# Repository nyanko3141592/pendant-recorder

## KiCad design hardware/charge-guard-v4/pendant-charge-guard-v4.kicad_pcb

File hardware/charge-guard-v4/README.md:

# Charge guard v4 — engineering prototype, not for order

Existing v3 remains unchanged for the separate fit-check chat. This revision adds12parts (87total) within18×33×0.8mm/6layers; case integration is not established. Final KiCad ERC0/DRC0/unconnected0/schematic parity0. Review `order-status.json` and the final DRC/ ERC reports rather than assuming completion from a router log.

## Electrical change

J2 pack NTC now feeds an independent ratiometric window comparator U12 (TLV7032DDFR). R37 excites the NTC from VBUS; R38/R39 and R40/R41 define provisional cold/hot thresholds. USB absence removes excitation, so these dividers do not consume battery current in intended operation.

U12A is high when NTC voltage is below the cold reference; U12B is high when above the hot reference. NTC open gives cold-not-OK; short gives hot-not-OK. The push-pull TLV7032 has POR-low outputs; the open-drain TLV7042 has POR-high-impedance and must NOT be substituted. [TI SLVSE13J, sections4.2,5.9,6.4](https://www.ti.com/lit/ds/symlink/tlv7042.pdf).

Q2 clamps charger TS low by default through R12's VBUS pull-up. Q4/Q5/Q6 form a series permission path to release Q2 only when MCU CHG_ALLOW and both comparator outputs are high. R36 keeps CHG_ALLOW low at reset. MCU GPIO is no longer directly tied to the inhibit gate; no5V GPIO pull-up is introduced. Body diode orientation of each series NMOS opposes the downward current when off.

Charger TS uses R35=10k to GND when released. This prevents the intended circuit from leaving TS floating. The existing BQ25101 permits TTDM with a floating/high TS, which disables temperature monitoring/timer/termination: [TI SLUSBV8C pin table](https://www.ti.com/lit/ds/symlink/bq25101.pdf). The NTC is no longer placed directly on that pin. Charge voltage/current regulation remains BQ25101; external guard replaces its temperature decision.

## What the analysis does and does not establish

`check_guard.py` checks actual net assignments, all8Boolean permission combinations, open/short faults, and resistor/comparator-error DC corners. Hypothetical R25=9..11k and beta2000..5000K produce conditional cold trips10.05..24.34°C and hot trips25.52..41.21°C. These are sensitivity bounds, NOT the actual XE temperature limits or a supplier-qualified guarantee. The broad uncertainty can leave only a narrow usable range; do not publish this as the final user operating range.

The33mV total comparator error allowance is a design assumption. TI's dual electrical table covers1.8..5V, whereas the study includes5.25V USB; manufacturer confirmation/bench characterization is needed. Actual NTC beta/R-T tolerances, thermal lag/self-heating, MOS leakage, switching thresholds, power ramp timing, TS disable levels and brownouts still require qualification. Nominal5V divider consumption is about0.75mA from USB (including inhibit pull-up when released), and typical NTC dissipation near25°C is0.625mW; pack thermal effect is unknown.

No charging permission may be enabled in released firmware until the battery-specific guard configuration and charge voltage/termination conditions are approved. During boot/reset/suspend/error, CHG_ALLOW stays low. Normal USB insertion must preserve recording and must not request USB sync.

## Reproduction

1. `python3 hardware/tools/create_charge_guard_v4.py` creates schematic/BOM/connection table (overwrites those files).
2. KiCad Python `hardware/tools/prepare_charge_guard_board.py` makes a new unrouted seed from v3.
3. KiCad Python `hardware/tools/layout_charge_guard_v4.py --discard-routing` packs the87parts and exports route.dsn. This overwrites this revision's board.
4. Freerouting2.5.0: `-de route.dsn -do route.ses -mp25 --router.optimizer.enabled=false`.
5. Import with the dedicated tool, normalize minimum width0.10mm, apply `hardware/tools/finish_charge_guard_v4.py`, then run KiCad DRC with schematic parity and ERC. The repair moves shared endpoints/vias0.015..0.030mm, keeping0.10mm clearance.
6. `python3 hardware/charge-guard-v4/check_guard.py` regenerates the conditional DC analysis.

All additions require assembled-board sourcing/DFM. `sourcing-delta.json` lists catalog candidates, not reserved stock or an accepted order BOM. The earlier pending charge-voltage, termination, firmware, USB/SI and actual harness constraints remain.

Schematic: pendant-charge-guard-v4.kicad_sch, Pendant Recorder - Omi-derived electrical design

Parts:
C1, C2, C3, C6, C9, C22, C23, C24, C26: 100n; C_0402_1005Metric
C4: 10u; C_0603_1608Metric
C5, C15: 4.7u; C_0603_1608Metric
C7, C16, C18, C19, C25: 1u; C_0402_1005Metric
C11, C12: 10p tentative; C_0402_1005Metric
C13: 2.2u 10V; C_0402_1005Metric
C14: 2.2u; C_0402_1005Metric
C27: 22u effective TBD; C_0603_1608Metric
C28: 10n; C_0402_1005Metric
C29: 100n 10V; C_0402_1005Metric
D1: red LED; LED_0402_1005Metric
D2: BAT54WS (candidate; leakage/forward drop review p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; D_SOD-323
D6: amber LED 0402 TBD; LED_0402_1005Metric
J1: USB4105-GF-A (candidate); USB_C_GCT_USB4105_GroundLand112
J2: 0781710003 / DTP401525-XE; Molex_Pico-EZmate_78171-0003_1x03-1MP_P1.20mm_Vertical
J3: TC2030 SWD target pads; Tag-Connect_TC2030-IDC-NL_2x03_P1.27mm_Vertical
Q1: DMP2035U (candidate; power path review pending); SOT-23
Q2: 2N7002 (charge inhibit); SOT-23
Q3: 2N7002 (VBUS detect); SOT-23
Q4, Q5, Q6: 2N7002; SOT-23
R1: 0R; R_0402_1005Metric
R2: 10k; R_0402_1005Metric
R3, R4, R11, R12, R13, R15, R16, R17, R22, R36: 100k; R_0402_1005Metric
R5: 3.3k; R_0402_1005Metric
R6, R7: 5.1k 1%; R_0402_1005Metric
R8, R9: 0R tuning; R_0402_1005Metric
R10: 6.19k 1%; R_0402_1005Metric
R14: 1M; R_0402_1005Metric
R21, R23: 22R tentative; R_0402_1005Metric
R24, R25, R28: 47k; R_0402_1005Metric
R32: 6.8k tentative; R_0402_1005Metric
R33, R34: 1M 1%; R_0402_1005Metric
R35, R37, R38, R40: 10k 1%; R_0402_1005Metric
R39: 12.1k 1%; R_0402_1005Metric
R41: 8.25k 1%; R_0402_1005Metric
SW1: B3U-1000P (candidate); SW_SPST_B3U-1000P
TP1, TP2, TP3, TP4, TP5, TP6: TestPoint; TestPoint_Pad_D1.0mm
U1: STM32U535CEU6; QFN-48-1EP_7x7mm_P0.5mm_EP5.6x5.6mm
U2: USBLC6-2P6; SOT-666
U3: BQ25101YFPR; BQ25101_YFP6
U4: TPS7A0233PDBVR; SOT-23-5
U6: TPS7A0218PDBVR; SOT-23-5
U8: T5838; T5838_LGA7_BottomPort
U9: TXS0104ERUTR; Texas_R-PUQFN-N12
U10: TPS22916CYFPR; TPS22916_YFP4
U11: CSNP32GCR01-BOW; CSNP32GCR01_LGA8
U12: TLV7032DDFR; SOT-23-8
Y1: 32.768kHz CL=7pF TBD; Crystal_SMD_2012-2Pin_2.0x1.2mm

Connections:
/ALLOW_CHAIN_1: Q4.3 (D), Q5.2 (S)
/ALLOW_CHAIN_2: Q5.3 (D), Q6.2 (S)
/BAT: C14.1, J2.1 (PACK+), Q1.3 (D), R33.1, TP1.1, U3.A1 (OUT)
/BAT_ADC: C28.1, R33.2, R34.1, U1.11 (PA1)
/BAT_TS: J2.2 (PACK_NTC), R37.2, U12.2 (INA-), U12.5 (INB+)
/BOOT0: R3.1, U1.44 (PH3)
/BUTTON_N: R4.2, SW1.1, U1.26 (PB13)
/CC1: J1.A5 (CC1), R6.1
/CC2: J1.B5 (CC2), R7.1
/CHARGER_TS: Q2.3 (D), R35.1, U3.B1 (TS)
/CHG_ALLOW: Q4.1 (G), R36.1, U1.20 (PB2)
/CHG_INHIBIT_GATE: Q2.1 (G), Q6.3 (D), R12.2
/CHG_N: R11.2, U1.27 (PB14), U3.C1 (CHG)
/GND: C1.2, C2.2, C3.2, C4.2, C5.2, C6.2, C7.2, C9.2, C11.2, C12.2, C13.2, C14.2, C15.2, C16.2, C18.2, C19.2, C22.2, C23.2, C24.2, C25.2, C26.2, C27.2, C28.2, C29.2, D1.1 (K), D6.1 (K), J1.A1 (GND), J1.A12 (GND), J1.B1 (GND), J1.B12 (GND), J1.SH (SHIELD), J2.3 (PACK-), J3.5 (GND), Q2.2 (S), Q3.2 (S), Q4.2 (S), R3.2, R6.2, R7.2, R10.2, R14.2, R16.2, R17.2, R22.2, R34.2, R35.2, R36.2, R39.2, R41.2, SW1.2, TP6.1, U1.8 (VSSA), U1.23 (VSS), U1.35 (VSS), U1.47 (VSS), U1.49 (VSS), U2.2 (GND), U3.C2 (VSS), U4.2 (GND), U6.2 (GND), U8.2 (SELECT), U8.3 (GND), U9.6 (GND), U10.B1 (GND), U11.4 (VSS), U12.4 (VEE)
/ISET: R10.1, U3.B2 (ISET)
/LED_A: D1.2 (A), R5.2
/LSE_IN: C11.1, U1.3 (PC14), Y1.1
/LSE_OUT: C12.1, U1.4 (PC15), Y1.2
/MIC_CLK_1V8: U8.6 (CLK), U9.5 (A4)
/MIC_DATA_1V8: U8.1 (DATA), U9.4 (A3)
/MIC_EN: R17.1, U1.41 (PB5), U6.3 (EN)
/MIC_THSEL: U1.13 (PA3), U9.9 (B2)
/MIC_THSEL_1V8: U8.5 (THSEL), U9.3 (A2)
/MIC_WAKE: U1.12 (PA2), U9.10 (B1)
/MIC_WAKE_1V8: U8.4 (WAKE), U9.2 (A1)
/NRST: C9.1, J3.3 (nRESET), R2.2, U1.7 (NRST)
/PDM_CLK: R21.2, U9.7 (B4)
/PDM_CLK_MCU: R21.1, U1.39 (PB3)
/PDM_DATA: U1.40 (PB4), U9.8 (B3)
/REC_LED: R5.1, U1.25 (PB12)
/SD_CLK: R23.2, U11.3 (CLK)
/SD_CLK_MCU: R23.1, U1.15 (PA5)
/SD_CS_N: R28.2, U1.14 (PA4), U11.2 (CS_N)
/SD_EN: R22.1, U1.18 (PB0), U10.B2 (ON)
/SD_MISO: R25.2, U1.16 (PA6), U11.6 (DO)
/SD_MOSI: R24.2, U1.17 (PA7), U11.5 (DI)
/SD_V3: C26.1, C27.1, R24.1, R25.1, R28.1, TP5.1, U10.A1 (VOUT), U11.8 (VCC)
/STATUS_LED: R32.1, U1.29 (PA8)
/STATUS_LED_A: D6.2 (A), R32.2
/SWCLK: J3.4 (SWCLK), U1.37 (PA14)
/SWDIO: J3.2 (SWDIO), U1.34 (PA13)
/SYS: C15.1, D2.1 (K), Q1.2 (S), TP2.1, U4.1 (IN), U4.3 (EN)
/TEMP_COLD_OK: Q5.1 (G), U12.1 (OUTA)
/TEMP_HOT_OK: Q6.1 (G), U12.7 (OUTB)
/TS_COLD_REF: R38.2, R39.1, U12.3 (INA+)
/TS_HOT_REF: R40.2, R41.1, U12.6 (INB-)
/USB_DM: J1.A7 (D-), J1.B7 (D-), R9.1, U2.3 (IO2), U2.4 (IO2)
/USB_DM_MCU: R9.2, U1.32 (PA11)
/USB_DP: J1.A6 (D+), J1.B6 (D+), R8.1, U2.1 (IO1), U2.6 (IO1)
/USB_DP_MCU: R8.2, U1.33 (PA12)
/V1V8: C18.1, C22.1, C23.1, TP4.1, U6.5 (OUT), U8.7 (VDD), U9.1 (VCCA), U9.12 (OE)
/V3V3: C1.1, C2.1, C3.1, C4.1, C16.1, C19.1, C24.1, C25.1, J3.1 (VTref), R1.1, R2.1, R4.1, R11.1, R15.1, TP3.1, U1.1 (VBAT), U1.24 (VDD), U1.36 (VDD), U1.48 (VDD), U4.5 (OUT), U6.1 (IN), U9.11 (VCCB), U10.A2 (VIN)
/VBUS: C13.1, C29.1, D2.2 (A), J1.A4 (VBUS), J1.A9 (VBUS), J1.B4 (VBUS), J1.B9 (VBUS), Q1.1 (G), R12.1, R13.1, R16.1, R37.1, R38.1, R40.1, U2.5 (VBUS), U3.A2 (IN), U12.8 (VCC)
/VBUS_GATE: Q3.1 (G), R13.2, R14.1
/VBUS_N: Q3.3 (D), R15.2, U1.10 (PA0)
/VCAP: C5.1, U1.22 (VCAP)
/VDDA: C6.1, C7.1, R1.2, U1.9 (VDDA)

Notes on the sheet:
01 MCU / RTC / UI
02 USB-C / CHARGER
03 POWER / FUEL GAUGE
04 AUDIO / SD / INDICATORS
ENGINEERING DRAFT - NOT FOR FABRICATION - See hardware/charge-guard-v4/README.md

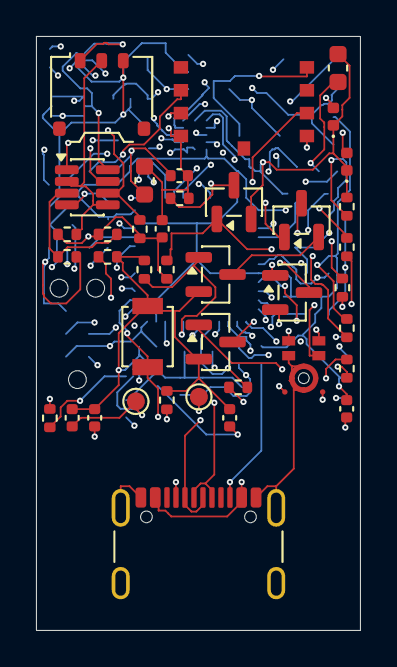
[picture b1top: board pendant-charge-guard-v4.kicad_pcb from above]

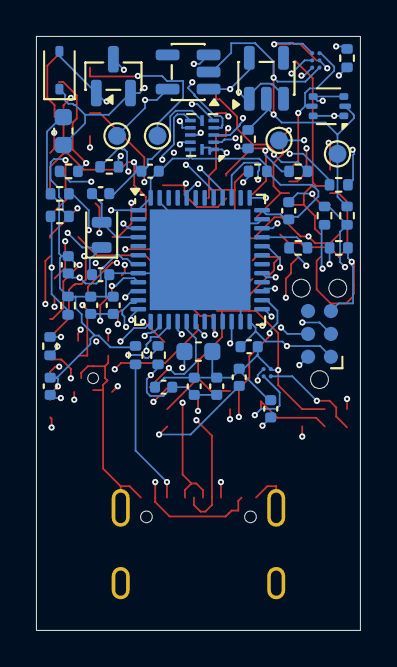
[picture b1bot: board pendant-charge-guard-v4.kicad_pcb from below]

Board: 6 copper layers, 18.0 x 33.0 mm, 87 parts (48 on the bottom side), 57 nets.

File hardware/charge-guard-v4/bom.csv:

Reference,Part/value,Footprint,Design note
U1,STM32U535CEU6,Package_DFN_QFN:QFN-48-1EP_7x7mm_P0.5mm_EP5.6x5.6mm,512KB Flash/274KB RAM; non-SMPS UFQFPN48. PB3/PB4 ADF AF3; PA5/6/7 SPI1 AF5. VDD USB shared 3.3V. JLC acceptance and pin review pending.
C1,100n,Capacitor_SMD:C_0402_1005Metric,
C4,10u,Capacitor_SMD:C_0603_1608Metric,Main bulk capacitor; check startup and effective capacitance.
C9,100n,Capacitor_SMD:C_0402_1005Metric,
R2,10k,Resistor_SMD:R_0402_1005Metric,
Y1,32.768kHz CL=7pF TBD,Crystal:Crystal_SMD_2012-2Pin_2.0x1.2mm,
C11,10p tentative,Capacitor_SMD:C_0402_1005Metric,
C12,10p tentative,Capacitor_SMD:C_0402_1005Metric,
J3,TC2030 SWD target pads,Connector:Tag-Connect_TC2030-IDC-NL_2x03_P1.27mm_Vertical,TC2030-NL/CTX standard; completed STM32-compatible probe/cable; access with battery disconnected.
SW1,B3U-1000P (candidate),Button_Switch_SMD:SW_SPST_B3U-1000P,
R4,100k,Resistor_SMD:R_0402_1005Metric,
R5,3.3k,Resistor_SMD:R_0402_1005Metric,
D1,red LED,LED_SMD:LED_0402_1005Metric,
J1,USB4105-GF-A (candidate),PendantD1:USB_C_GCT_USB4105_GroundLand112,Exact footprint and shield pad numbering pending connector selection
R6,5.1k 1%,Resistor_SMD:R_0402_1005Metric,
R7,5.1k 1%,Resistor_SMD:R_0402_1005Metric,
R8,0R tuning,Resistor_SMD:R_0402_1005Metric,STM32 integrated USB termination; external series value validate against ST USB layout guidance.
R9,0R tuning,Resistor_SMD:R_0402_1005Metric,STM32 integrated USB termination; external series value validate against ST USB layout guidance.
U2,USBLC6-2P6,Package_TO_SOT_SMD:SOT-666,"ST DS4260 same 6-pin function diagram; smaller package, LCSC C15999 catalog; orientation/land pattern final audit pending."
C13,2.2u 10V,Capacitor_SMD:C_0402_1005Metric,
U3,BQ25101YFPR,Pendant:BQ25101_YFP6,BQ25101 charge regulation retained; TS driven by independent hardware window guard and fixed10k. Not directly connected to pack NTC.
R10,6.19k 1%,Resistor_SMD:R_0402_1005Metric,"Nominal21.81mA, upper estimate23.66mA. XE charge current/termination/voltage acceptance not finalized."
R11,100k,Resistor_SMD:R_0402_1005Metric,
C14,2.2u,Capacitor_SMD:C_0402_1005Metric,
J2,0781710003 / DTP401525-XE,Connector_Molex:Molex_Pico-EZmate_78171-0003_1x03-1MP_P1.20mm_Vertical,"Pack NTC goes to separate window comparator, not charger TS. Beta/tolerances need supplier confirmation."
Q2,2N7002 (charge inhibit),Package_TO_SOT_SMD:SOT-23,Default-on TS clamp. Only MCU permission AND both hardware temperature permissions release it. Validate start-up transients.
R12,100k,Resistor_SMD:R_0402_1005Metric,100k VBUS pull-up defaults Q2 to charge inhibited; no MCU GPIO connection to5V.
D2,BAT54WS (candidate; leakage/forward drop review pending),Diode_SMD:D_SOD-323,USB path; characterize leakage and input inrush
Q1,DMP2035U (candidate; power path review pending),Package_TO_SOT_SMD:SOT-23,"S=SYS, D=BAT intentionally; body diode BAT -> SYS; exact MPN/pinout pending"
R16,100k,Resistor_SMD:R_0402_1005Metric,
C15,4.7u,Capacitor_SMD:C_0603_1608Metric,
U4,TPS7A0233PDBVR,Package_TO_SOT_SMD:SOT-23-5,3.3V main rail: 48-pin MCU has no separate USB supply; dropout/capacity measurement required.
U6,TPS7A0218PDBVR,Package_TO_SOT_SMD:SOT-23-5,DBV / SOT23-5 prototype; miniaturization later
C16,1u,Capacitor_SMD:C_0402_1005Metric,
C18,1u,Capacitor_SMD:C_0402_1005Metric,
C19,1u,Capacitor_SMD:C_0402_1005Metric,
R17,100k,Resistor_SMD:R_0402_1005Metric,
U8,T5838,Pendant:T5838_LGA7_BottomPort,BOTTOM port; 1.62..1.98V only; SELECT low = right channel
U9,TXS0104ERUTR,Package_DFN_QFN:Texas_R-PUQFN-N12,TI SCES651K Table 5-4 RUT pinout. UQFN procurement and PCBA acceptance pending.
R21,22R tentative,Resistor_SMD:R_0402_1005Metric,
C22,100n,Capacitor_SMD:C_0402_1005Metric,
C23,100n,Capacitor_SMD:C_0402_1005Metric,
C24,100n,Capacitor_SMD:C_0402_1005Metric,
U10,TPS22916CYFPR,Pendant:TPS22916_YFP4,Omi SD switch; power-off sequence must tristate ALL SD signals
R22,100k,Resistor_SMD:R_0402_1005Metric,
C25,1u,Capacitor_SMD:C_0402_1005Metric,
U11,CSNP32GCR01-BOW,Pendant:CSNP32GCR01_LGA8,SPI mode per manufacturer p2; unused DAT1/DAT2 reserved; verify power-up and interrupted-write behavior.
R23,22R tentative,Resistor_SMD:R_0402_1005Metric,
R24,47k,Resistor_SMD:R_0402_1005Metric,
R25,47k,Resistor_SMD:R_0402_1005Metric,
R28,47k,Resistor_SMD:R_0402_1005Metric,
C26,100n,Capacitor_SMD:C_0402_1005Metric,
C27,22u effective TBD,Capacitor_SMD:C_0603_1608Metric,
TP1,TestPoint,TestPoint:TestPoint_Pad_D1.0mm,
TP2,TestPoint,TestPoint:TestPoint_Pad_D1.0mm,
TP3,TestPoint,TestPoint:TestPoint_Pad_D1.0mm,
TP4,TestPoint,TestPoint:TestPoint_Pad_D1.0mm,
TP5,TestPoint,TestPoint:TestPoint_Pad_D1.0mm,
TP6,TestPoint,TestPoint:TestPoint_Pad_D1.0mm,
R32,6.8k tentative,Resistor_SMD:R_0402_1005Metric,"LED current target 0.1-0.2mA; verify LED Vf, daylight readability and GPIO limits"
D6,amber LED 0402 TBD,LED_SMD:LED_0402_1005Metric,Battery level by blink count; shared charging/error indication; exact LED MPN pending.
C2,100n,Capacitor_SMD:C_0402_1005Metric,
C3,100n,Capacitor_SMD:C_0402_1005Metric,
C5,4.7u,Capacitor_SMD:C_0603_1608Metric,
C6,100n,Capacitor_SMD:C_0402_1005Metric,
C7,1u,Capacitor_SMD:C_0402_1005Metric,
R1,0R,Resistor_SMD:R_0402_1005Metric,
R3,100k,Resistor_SMD:R_0402_1005Metric,
Q3,2N7002 (VBUS detect),Package_TO_SOT_SMD:SOT-23,
R13,100k,Resistor_SMD:R_0402_1005Metric,
R14,1M,Resistor_SMD:R_0402_1005Metric,
R15,100k,Resistor_SMD:R_0402_1005Metric,
R33,1M 1%,Resistor_SMD:R_0402_1005Metric,"Battery divider 1:2; sample after settling, calibrate with VREFINT; not coulomb counting."
R34,1M 1%,Resistor_SMD:R_0402_1005Metric,"Battery divider 1:2; sample after settling, calibrate with VREFINT; not coulomb counting."
C28,10n,Capacitor_SMD:C_0402_1005Metric,"Battery divider 1:2; sample after settling, calibrate with VREFINT; not coulomb counting."
R35,10k 1%,Resistor_SMD:R_0402_1005Metric,Holds normal TS level when released; no floating TS/TTDM in intended circuit.
R36,100k,Resistor_SMD:R_0402_1005Metric,MCU reset/high-Z defaults to no charging permission.
R37,10k 1%,Resistor_SMD:R_0402_1005Metric,Ratiometric NTC excitation only while USB present; self-heating must be verified.
R38,10k 1%,Resistor_SMD:R_0402_1005Metric,
R39,12.1k 1%,Resistor_SMD:R_0402_1005Metric,Provisional narrow window. Final values require actual pack R-T curve.
R40,10k 1%,Resistor_SMD:R_0402_1005Metric,
R41,8.25k 1%,Resistor_SMD:R_0402_1005Metric,Provisional narrow window. Final values require actual pack R-T curve.
U12,TLV7032DDFR,Package_TO_SOT_SMD:SOT-23-8,Push-pull variant intentionally selected: POR outputs low. Do not substitute TLV7042 open-drain (POR high-Z). TI SLVSE13J pinout table4-2.
Q4,2N7002,Package_TO_SOT_SMD:SOT-23,Series pull-down permission chain. All three must conduct to release Q2. Body diodes oppose pull-down when off. Verify stack/leakage/transients.
Q5,2N7002,Package_TO_SOT_SMD:SOT-23,Series pull-down permission chain. All three must conduct to release Q2. Body diodes oppose pull-down when off. Verify stack/leakage/transients.
Q6,2N7002,Package_TO_SOT_SMD:SOT-23,Series pull-down permission chain. All three must conduct to release Q2. Body diodes oppose pull-down when off. Verify stack/leakage/transients.
C29,100n 10V,Capacitor_SMD:C_0402_1005Metric,Place adjacent to U12 supply pins.
